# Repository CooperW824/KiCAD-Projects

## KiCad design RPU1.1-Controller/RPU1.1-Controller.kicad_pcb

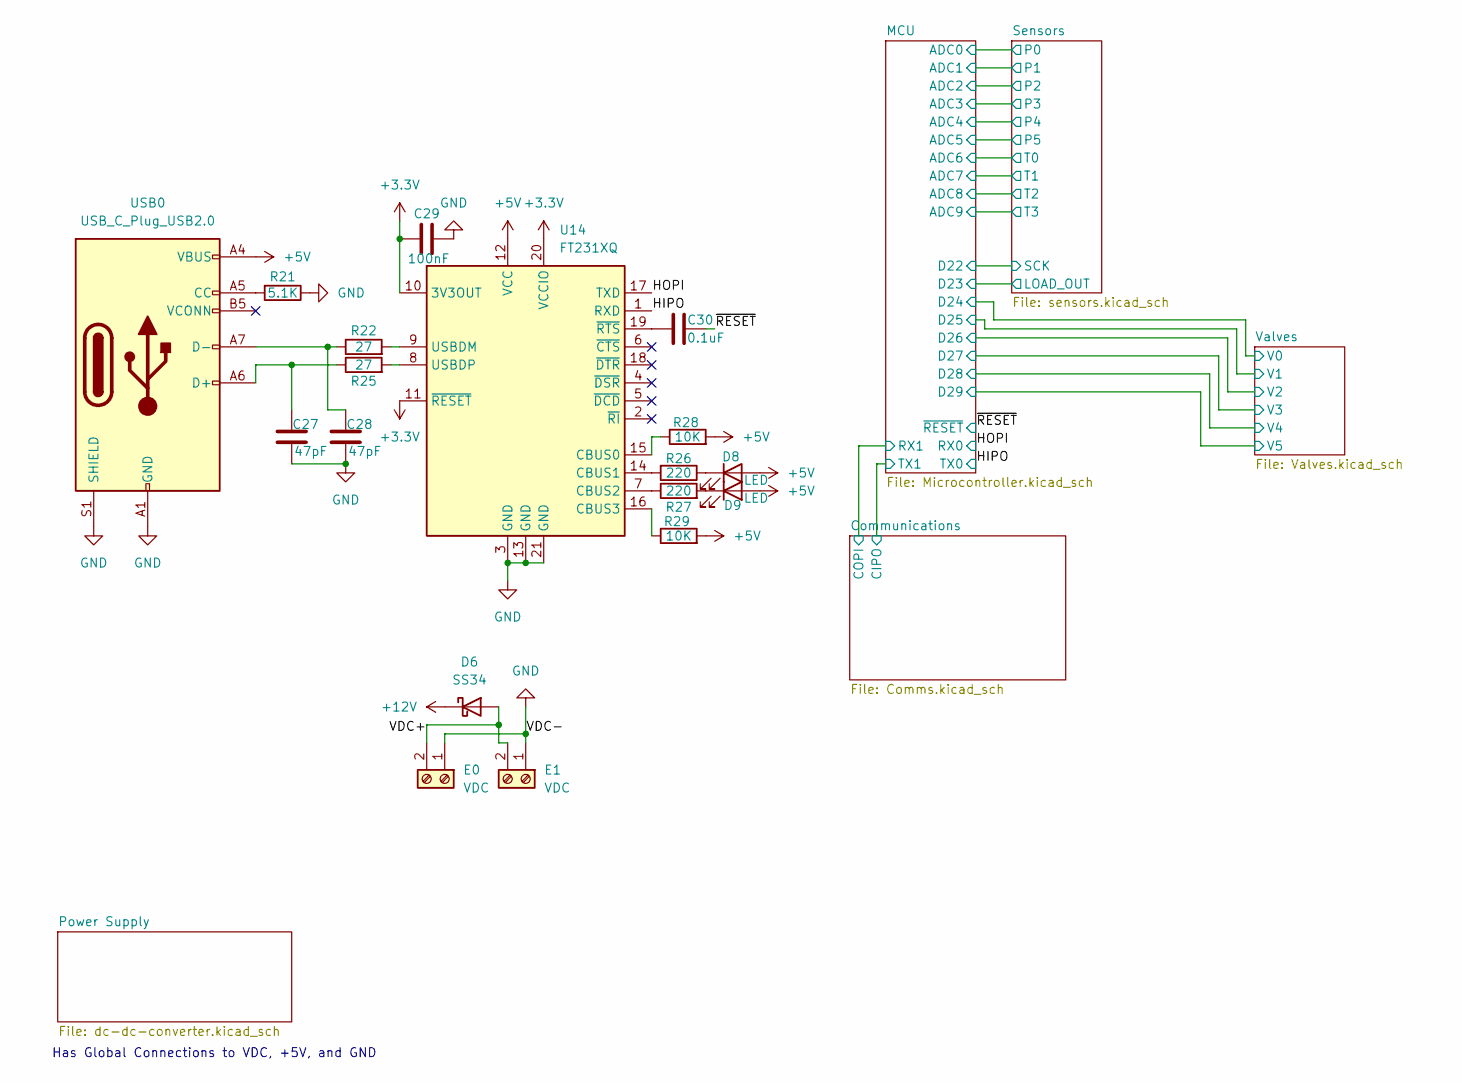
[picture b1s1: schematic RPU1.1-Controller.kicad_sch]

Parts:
C27, C28: 47pF; C_0603_1608Metric_Pad1.08x0.95mm_HandSolder
C29: 100nF; C_0603_1608Metric_Pad1.08x0.95mm_HandSolder
C30: 0.1uF; C_0603_1608Metric_Pad1.08x0.95mm_HandSolder
D6: SS34; D_SMA
D8, D9: LED; LED_0603_1608Metric
E0, E1: VDC; TerminalBlock_bornier-2_P5.08mm
R21: 5.1K; R_0603_1608Metric_Pad0.98x0.95mm_HandSolder
R22, R25: 27; R_0603_1608Metric_Pad0.98x0.95mm_HandSolder
R26, R27: 220; R_0603_1608Metric_Pad0.98x0.95mm_HandSolder
R28, R29: 10K; R_0603_1608Metric_Pad0.98x0.95mm_HandSolder
U14: FT231XQ; QFN-20-1EP_4x4mm_P0.5mm_EP2.5x2.5mm
USB0: USB_C_Plug_USB2.0; USB_C_Receptacle_Amphenol_12401610E4-2A

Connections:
+3.3V: C29.1, U14.10 (3V3OUT), U14.11 (~RESET), U14.20 (VCCIO)
+5V: D8.2 (A), D9.2 (A), R28.2, R29.2, U14.12 (VCC), USB0.A4 (VBUS), USB0.A9 (VBUS), USB0.B4 (VBUS), USB0.B9 (VBUS); also elsewhere on the board
+12V: D6.1 (K); also elsewhere on the board
/HIPO: U14.1 (RXD); also elsewhere on the board
/HOPI: U14.17 (TXD); also elsewhere on the board
/VDC+: D6.2 (A), E0.2, E1.2
/~RESET: C30.2; also elsewhere on the board
GND: C27.2, C28.2, C29.2, E0.1, E1.1, R21.1, U14.3 (GND), U14.13 (GND), U14.21 (GND), USB0.A1 (GND), USB0.A12 (GND), USB0.B1 (GND), USB0.B12 (GND), USB0.S1 (SHIELD); also elsewhere on the board
unnamed: D8.1 (K), R26.1
unnamed: D9.1 (K), R27.2
unnamed: R28.1, U14.15 (CBUS0)
unnamed: R26.2, U14.14 (CBUS1)
unnamed: R27.1, U14.7 (CBUS2)
unnamed: R29.1, U14.16 (CBUS3)
unnamed: R22.2, U14.9 (USBDM)
unnamed: R25.2, U14.8 (USBDP)
unnamed: C30.1, U14.19 (~RTS)
unnamed: R21.2, USB0.A5 (CC)
unnamed: C27.1, R25.1, USB0.A6 (D+)
unnamed: C28.1, R22.1, USB0.A7 (D-)

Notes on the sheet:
Has Global Connections to VDC, +5V, and GND

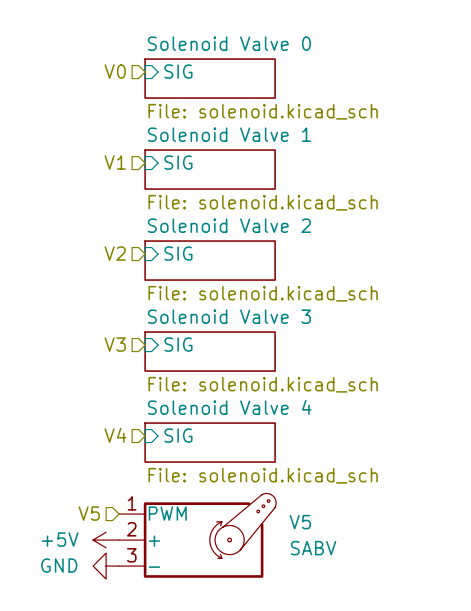
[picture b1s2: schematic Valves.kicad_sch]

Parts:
V5: SABV; TerminalBlock_bornier-3_P5.08mm

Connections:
+5V: V5.2 (+); also elsewhere on the board
/MCU/D29: V5.1 (PWM); also elsewhere on the board
GND: V5.3 (-); also elsewhere on the board

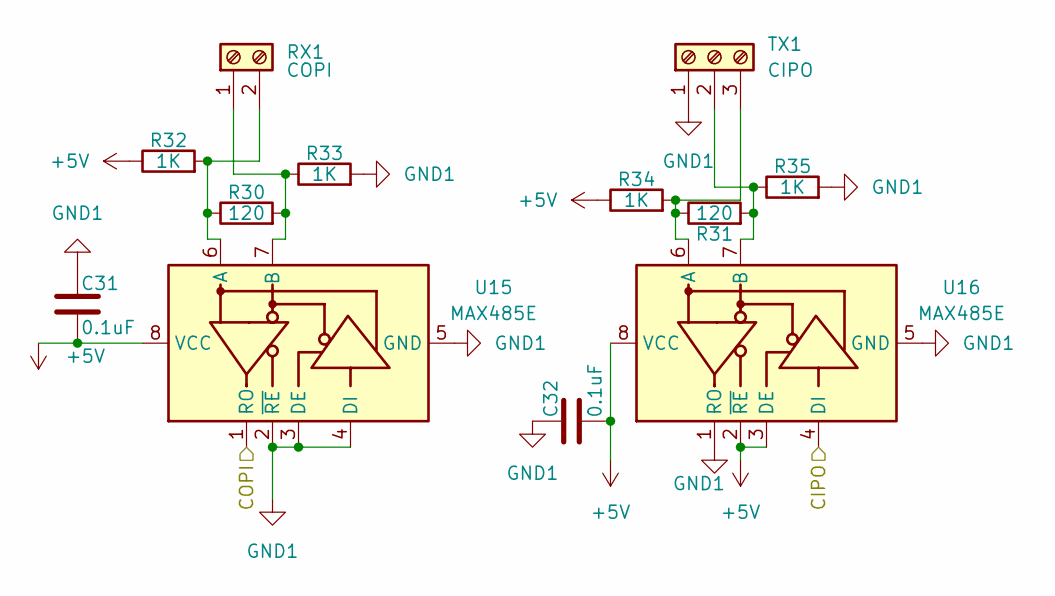
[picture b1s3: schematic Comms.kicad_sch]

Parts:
C31, C32: 0.1uF; C_0603_1608Metric_Pad1.08x0.95mm_HandSolder
R30, R31: 120; R_0603_1608Metric_Pad0.98x0.95mm_HandSolder
R32, R33, R34, R35: 1K; R_0603_1608Metric_Pad0.98x0.95mm_HandSolder
RX1: COPI; TerminalBlock_bornier-2_P5.08mm
TX1: CIPO; TerminalBlock_bornier-3_P5.08mm
U15, U16: MAX485E; SOIC-8_3.9x4.9mm_P1.27mm

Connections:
+5V: C31.2, C32.2, R32.1, R34.1, U15.8 (VCC), U16.2 (~RE), U16.3 (DE), U16.8 (VCC); also elsewhere on the board
/Communications/CIPO: U16.4 (DI); also elsewhere on the board
/Communications/COPI: U15.1 (RO); also elsewhere on the board
GND1: C31.1, C32.1, R33.2, R35.2, TX1.1, U15.2 (~RE), U15.3 (DE), U15.4 (DI), U15.5 (GND), U16.1 (RO), U16.5 (GND)
unnamed: R30.2, R33.1, RX1.1, U15.7 (B)
unnamed: R30.1, R32.2, RX1.2, U15.6 (A)
unnamed: R31.2, R35.1, TX1.2, U16.7 (B)
unnamed: R31.1, R34.2, TX1.3, U16.6 (A)

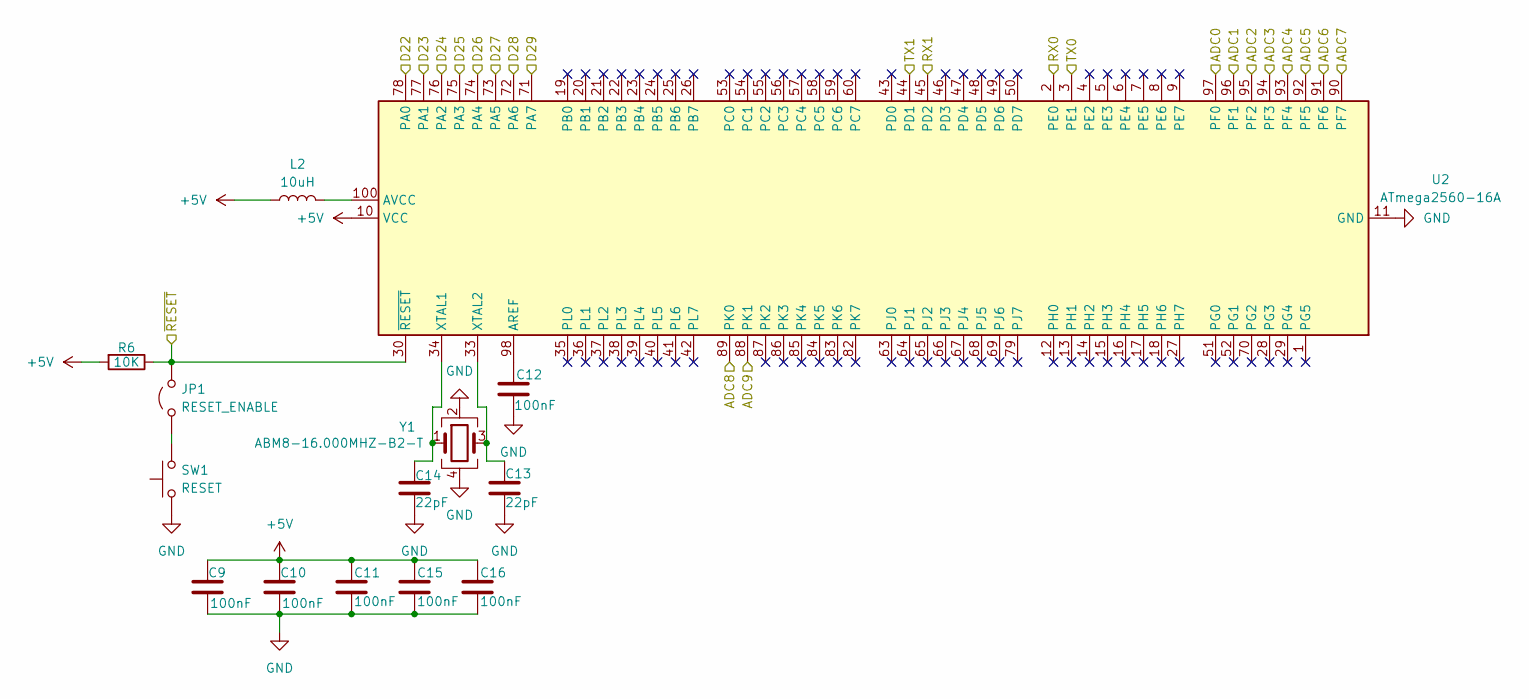
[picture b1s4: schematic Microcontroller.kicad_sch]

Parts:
C9, C10, C11, C12, C15, C16: 100nF; C_0603_1608Metric_Pad1.08x0.95mm_HandSolder
C13, C14: 22pF; C_0603_1608Metric_Pad1.08x0.95mm_HandSolder
JP1: RESET_ENABLE; PinHeader_1x02_P2.54mm_Vertical
L2: 10uH; L_0805_2012Metric_Pad1.15x1.40mm_HandSolder
R6: 10K; R_0603_1608Metric_Pad0.98x0.95mm_HandSolder
SW1: RESET; SW_PUSH_6mm
U2: ATmega2560-16A; TQFP-100_14x14mm_P0.5mm
Y1: ABM8-16.000MHZ-B2-T; Oscillator_SMD_Abracon_ASE-4Pin_3.2x2.5mm

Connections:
+5V: C9.1, C10.1, C11.1, C15.1, C16.1, L2.1, R6.2, U2.10 (VCC), U2.31 (VCC), U2.61 (VCC), U2.80 (VCC); also elsewhere on the board
/Communications/CIPO: U2.44 (PD1); also elsewhere on the board
/Communications/COPI: U2.45 (PD2); also elsewhere on the board
/HIPO: U2.3 (PE1); also elsewhere on the board
/HOPI: U2.2 (PE0); also elsewhere on the board
/MCU/ADC0: U2.97 (PF0); also elsewhere on the board
/MCU/ADC1: U2.96 (PF1); also elsewhere on the board
/MCU/ADC2: U2.95 (PF2); also elsewhere on the board
/MCU/ADC3: U2.94 (PF3); also elsewhere on the board
/MCU/ADC4: U2.93 (PF4); also elsewhere on the board
/MCU/ADC5: U2.92 (PF5); also elsewhere on the board
/MCU/ADC6: U2.91 (PF6); also elsewhere on the board
/MCU/ADC7: U2.90 (PF7); also elsewhere on the board
/MCU/ADC8: U2.89 (PK0); also elsewhere on the board
/MCU/ADC9: U2.88 (PK1); also elsewhere on the board
/MCU/D22: U2.78 (PA0); also elsewhere on the board
/MCU/D23: U2.77 (PA1); also elsewhere on the board
/MCU/D24: U2.76 (PA2); also elsewhere on the board
/MCU/D25: U2.75 (PA3); also elsewhere on the board
/MCU/D26: U2.74 (PA4); also elsewhere on the board
/MCU/D27: U2.73 (PA5); also elsewhere on the board
/MCU/D28: U2.72 (PA6); also elsewhere on the board
/MCU/D29: U2.71 (PA7); also elsewhere on the board
/~RESET: JP1.2 (B), R6.1, U2.30 (~RESET); also elsewhere on the board
GND: C9.2, C10.2, C11.2, C12.2, C13.2, C14.2, C15.2, C16.2, SW1.1, U2.11 (GND), U2.32 (GND), U2.62 (GND), U2.81 (GND), U2.99 (GND), Y1.2, Y1.4; also elsewhere on the board
unnamed: JP1.1 (A), SW1.2
unnamed: C12.1, U2.98 (AREF)
unnamed: L2.2, U2.100 (AVCC)
unnamed: C14.1, U2.34 (XTAL1), Y1.1
unnamed: C13.1, U2.33 (XTAL2), Y1.3

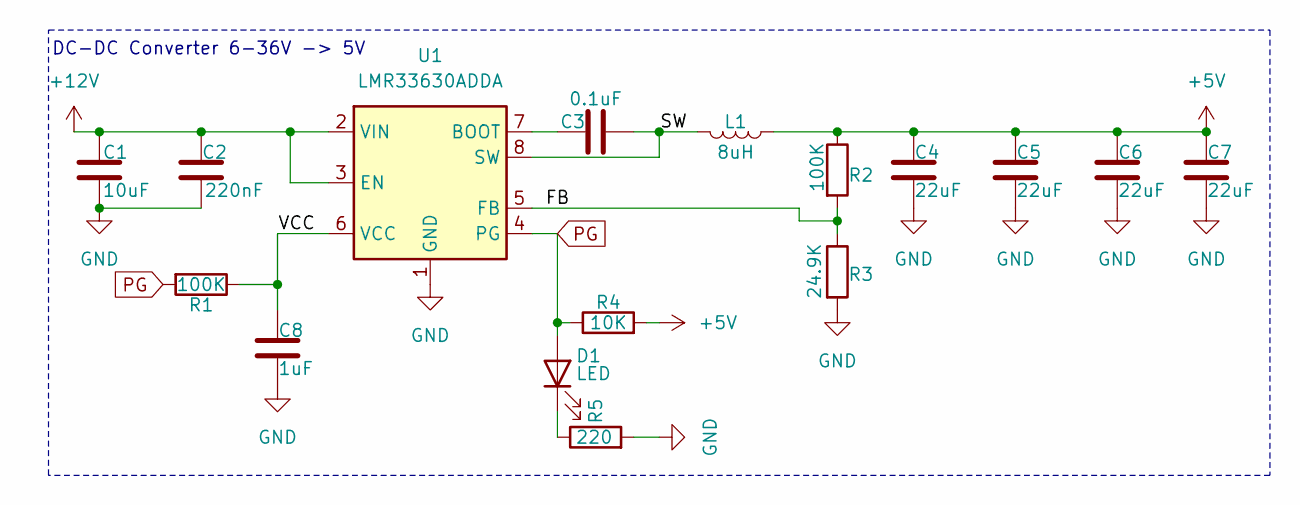
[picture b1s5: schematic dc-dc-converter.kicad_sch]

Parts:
C1: 10uF; C_0603_1608Metric
C2: 220nF; C_0402_1005Metric
C3: 0.1uF; C_0402_1005Metric
C4, C5, C6, C7: 22uF; C_0603_1608Metric
C8: 1uF; C_0402_1005Metric
D1: LED; LED_0603_1608Metric
L1: 8uH; L_0805_2012Metric
R1, R2: 100K; R_0603_1608Metric_Pad0.98x0.95mm_HandSolder
R3: 24.9K; R_0603_1608Metric_Pad0.98x0.95mm_HandSolder
R4: 10K; R_0603_1608Metric_Pad0.98x0.95mm_HandSolder
R5: 220; R_0603_1608Metric_Pad0.98x0.95mm_HandSolder
U1: LMR33630ADDA; Texas_HSOP-8-1EP_3.9x4.9mm_P1.27mm_ThermalVias

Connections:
+5V: C4.2, C5.2, C6.2, C7.2, L1.1, R2.1, R4.2; also elsewhere on the board
+12V: C1.1, C2.1, U1.2 (VIN), U1.3 (EN); also elsewhere on the board
/Power Supply/FB: R2.2, R3.1, U1.5 (FB)
/Power Supply/SW: C3.2, L1.2, U1.8 (SW)
/Power Supply/VCC: C8.2, R1.1, U1.6 (VCC)
GND: C1.2, C2.2, C4.1, C5.1, C6.1, C7.1, C8.1, R3.2, R5.2, U1.1 (GND), U1.9 (GND); also elsewhere on the board
unnamed: D1.1 (K), R5.1
unnamed: C3.1, U1.7 (BOOT)
PG: D1.2 (A), R1.2, R4.1, U1.4 (PG)

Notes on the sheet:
DC-DC Converter 6-36V -> 5V

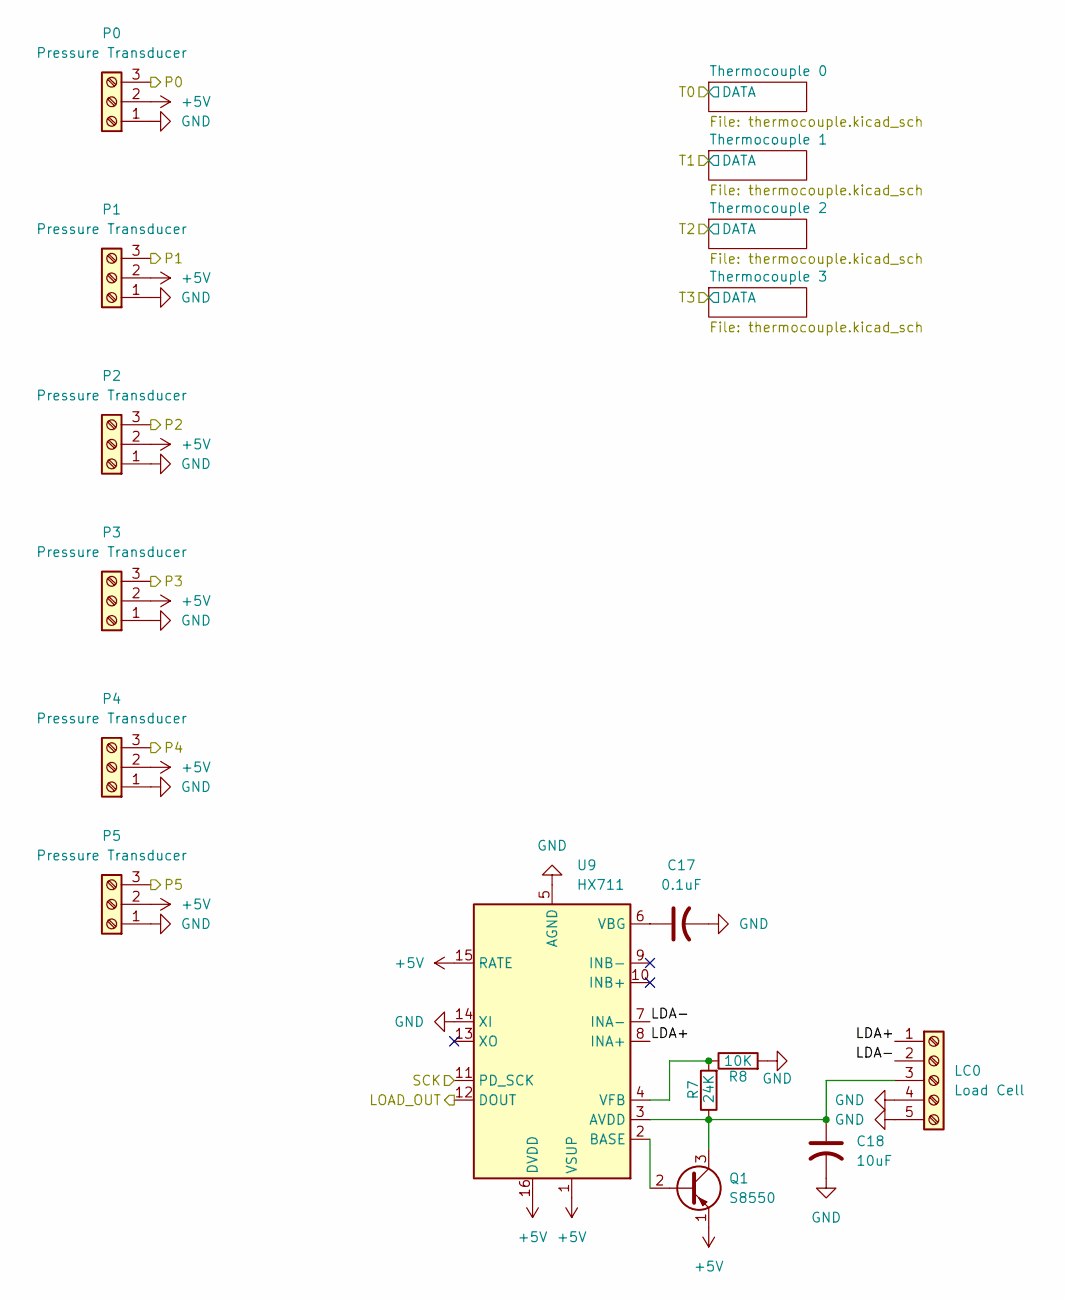
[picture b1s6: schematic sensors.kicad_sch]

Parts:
C17: 0.1uF; C_0603_1608Metric_Pad1.08x0.95mm_HandSolder
C18: 10uF; C_0603_1608Metric_Pad1.08x0.95mm_HandSolder
LC0: Load Cell; TerminalBlock_bornier-5_P5.08mm
P0, P1, P2, P3, P4, P5: Pressure Transducer; TerminalBlock_bornier-3_P5.08mm
Q1: S8550; SOT-23
R7: 24K; R_0603_1608Metric_Pad0.98x0.95mm_HandSolder
R8: 10K; R_0603_1608Metric_Pad0.98x0.95mm_HandSolder
U9: HX711; SOP-16_3.9x9.9mm_P1.27mm

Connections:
+5V: P0.2, P1.2, P2.2, P3.2, P4.2, P5.2, Q1.1 (E), U9.1 (VSUP), U9.15 (RATE), U9.16 (DVDD); also elsewhere on the board
/MCU/ADC0: P0.3; also elsewhere on the board
/MCU/ADC1: P1.3; also elsewhere on the board
/MCU/ADC2: P2.3; also elsewhere on the board
/MCU/ADC3: P3.3; also elsewhere on the board
/MCU/ADC4: P4.3; also elsewhere on the board
/MCU/ADC5: P5.3; also elsewhere on the board
/MCU/D22: U9.11 (PD_SCK); also elsewhere on the board
/MCU/D23: U9.12 (DOUT); also elsewhere on the board
/Sensors/LDA+: LC0.1, U9.8 (INA+)
/Sensors/LDA-: LC0.2, U9.7 (INA-)
GND: C17.2, C18.2, LC0.4, LC0.5, P0.1, P1.1, P2.1, P3.1, P4.1, P5.1, R8.2, U9.5 (AGND), U9.14 (XI); also elsewhere on the board
unnamed: C18.1, LC0.3, Q1.3 (C), R7.1, U9.3 (AVDD)
unnamed: Q1.2 (B), U9.2 (BASE)
unnamed: C17.1, U9.6 (VBG)
unnamed: R7.2, R8.1, U9.4 (VFB)

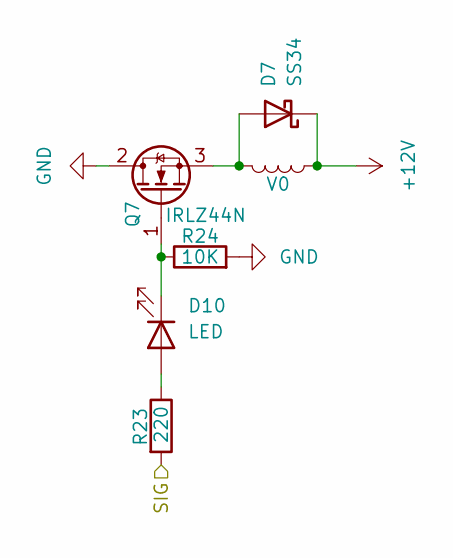
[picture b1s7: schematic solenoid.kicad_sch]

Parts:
D7: SS34; D_SMA
D10: LED; LED_D5.0mm
Q7: IRLZ44N; TO-220-3_Vertical
R23: 220; R_0603_1608Metric_Pad0.98x0.95mm_HandSolder
R24: 10K; R_0603_1608Metric_Pad0.98x0.95mm_HandSolder
V0: L; TerminalBlock_bornier-2_P5.08mm

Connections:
+12V: D7.1 (K), V0.1; also elsewhere on the board
/MCU/D24: R23.2; also elsewhere on the board
GND: Q7.2 (D), R24.2; also elsewhere on the board
unnamed: D7.2 (A), Q7.3 (S), V0.2
unnamed: D10.2 (A), R23.1
unnamed: D10.1 (K), Q7.1 (G), R24.1

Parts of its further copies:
D2, D3, D4, D5: SS34; D_SMA
D11, D12, D13, D14: LED; LED_D5.0mm
Q2, Q3, Q4, Q5: IRLZ44N; TO-220-3_Vertical
R13, R15, R17, R19: 220; R_0603_1608Metric_Pad0.98x0.95mm_HandSolder
R14, R16, R18, R20: 10K; R_0603_1608Metric_Pad0.98x0.95mm_HandSolder
V1, V2, V3, V4: L; TerminalBlock_bornier-2_P5.08mm

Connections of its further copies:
+12V: D2.1 (K), D3.1 (K), D4.1 (K), D5.1 (K), V1.1, V2.1, V3.1, V4.1; also elsewhere on the board
/MCU/D25: R13.2; also elsewhere on the board
/MCU/D26: R15.2; also elsewhere on the board
/MCU/D27: R17.2; also elsewhere on the board
/MCU/D28: R19.2; also elsewhere on the board
GND: Q2.2 (D), Q3.2 (D), Q4.2 (D), Q5.2 (D), R14.2, R16.2, R18.2, R20.2; also elsewhere on the board
unnamed: D2.2 (A), Q2.3 (S), V1.2
unnamed: D3.2 (A), Q3.3 (S), V2.2
unnamed: D4.2 (A), Q4.3 (S), V3.2
unnamed: D5.2 (A), Q5.3 (S), V4.2
unnamed: D11.2 (A), R15.1
unnamed: D11.1 (K), Q3.1 (G), R16.1
unnamed: D12.2 (A), R13.1
unnamed: D12.1 (K), Q2.1 (G), R14.1
unnamed: D13.2 (A), R17.1
unnamed: D13.1 (K), Q4.1 (G), R18.1
unnamed: D14.2 (A), R19.1
unnamed: D14.1 (K), Q5.1 (G), R20.1

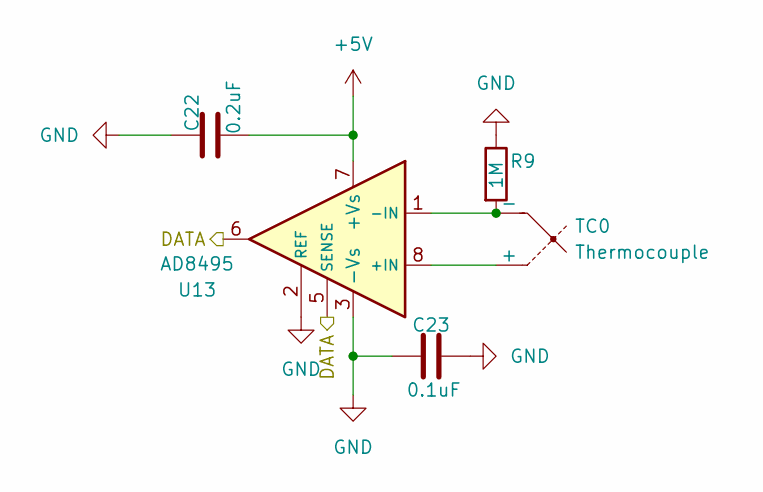
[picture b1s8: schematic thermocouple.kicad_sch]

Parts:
C22: 0.2uF; C_0603_1608Metric_Pad1.08x0.95mm_HandSolder
C23: 0.1uF; C_0603_1608Metric_Pad1.08x0.95mm_HandSolder
R9: 1M; R_0603_1608Metric_Pad0.98x0.95mm_HandSolder
TC0: Thermocouple; TerminalBlock_bornier-2_P5.08mm
U13: AD8495; MSOP-8_3x3mm_P0.65mm

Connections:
+5V: C22.2, U13.7 (+Vs); also elsewhere on the board
/MCU/ADC6: U13.5 (SENSE), U13.6; also elsewhere on the board
GND: C22.1, C23.1, C23.2, R9.1, U13.2 (REF), U13.3 (-Vs); also elsewhere on the board
unnamed: TC0.2 (+), U13.8 (+IN)
unnamed: R9.2, TC0.1 (-), U13.1 (-IN)

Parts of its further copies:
C20, C24, C26: 0.1uF; C_0603_1608Metric_Pad1.08x0.95mm_HandSolder
R10, R11, R12: 1M; R_0603_1608Metric_Pad0.98x0.95mm_HandSolder
TC1, TC2, TC3: Thermocouple; TerminalBlock_bornier-2_P5.08mm
U10, U11, U12: AD8495; MSOP-8_3x3mm_P0.65mm

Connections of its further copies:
+5V: U10.7 (+Vs), U11.7 (+Vs), U12.7 (+Vs); also elsewhere on the board
/MCU/ADC7: U10.5 (SENSE), U10.6; also elsewhere on the board
/MCU/ADC8: U11.5 (SENSE), U11.6; also elsewhere on the board
/MCU/ADC9: U12.5 (SENSE), U12.6; also elsewhere on the board
GND: C20.1, C20.2, C24.1, C24.2, C26.1, C26.2, R10.1, R11.1, R12.1, U10.2 (REF), U10.3 (-Vs), U11.2 (REF), U11.3 (-Vs), U12.2 (REF), U12.3 (-Vs); also elsewhere on the board
unnamed: TC1.2 (+), U10.8 (+IN)
unnamed: R10.2, TC1.1 (-), U10.1 (-IN)
unnamed: TC2.2 (+), U11.8 (+IN)
unnamed: R11.2, TC2.1 (-), U11.1 (-IN)
unnamed: TC3.2 (+), U12.8 (+IN)
unnamed: R12.2, TC3.1 (-), U12.1 (-IN)

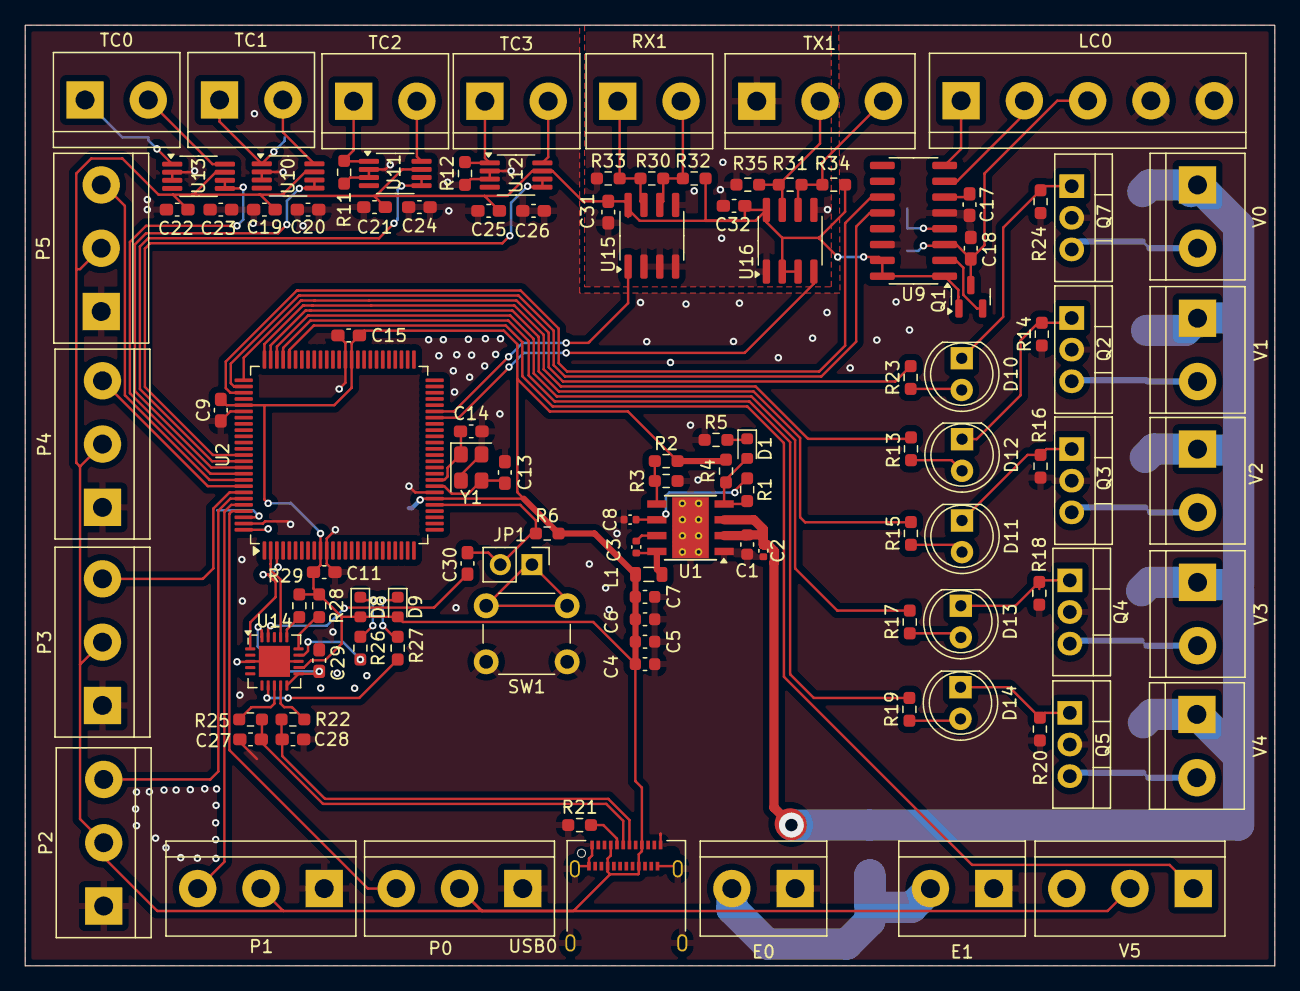
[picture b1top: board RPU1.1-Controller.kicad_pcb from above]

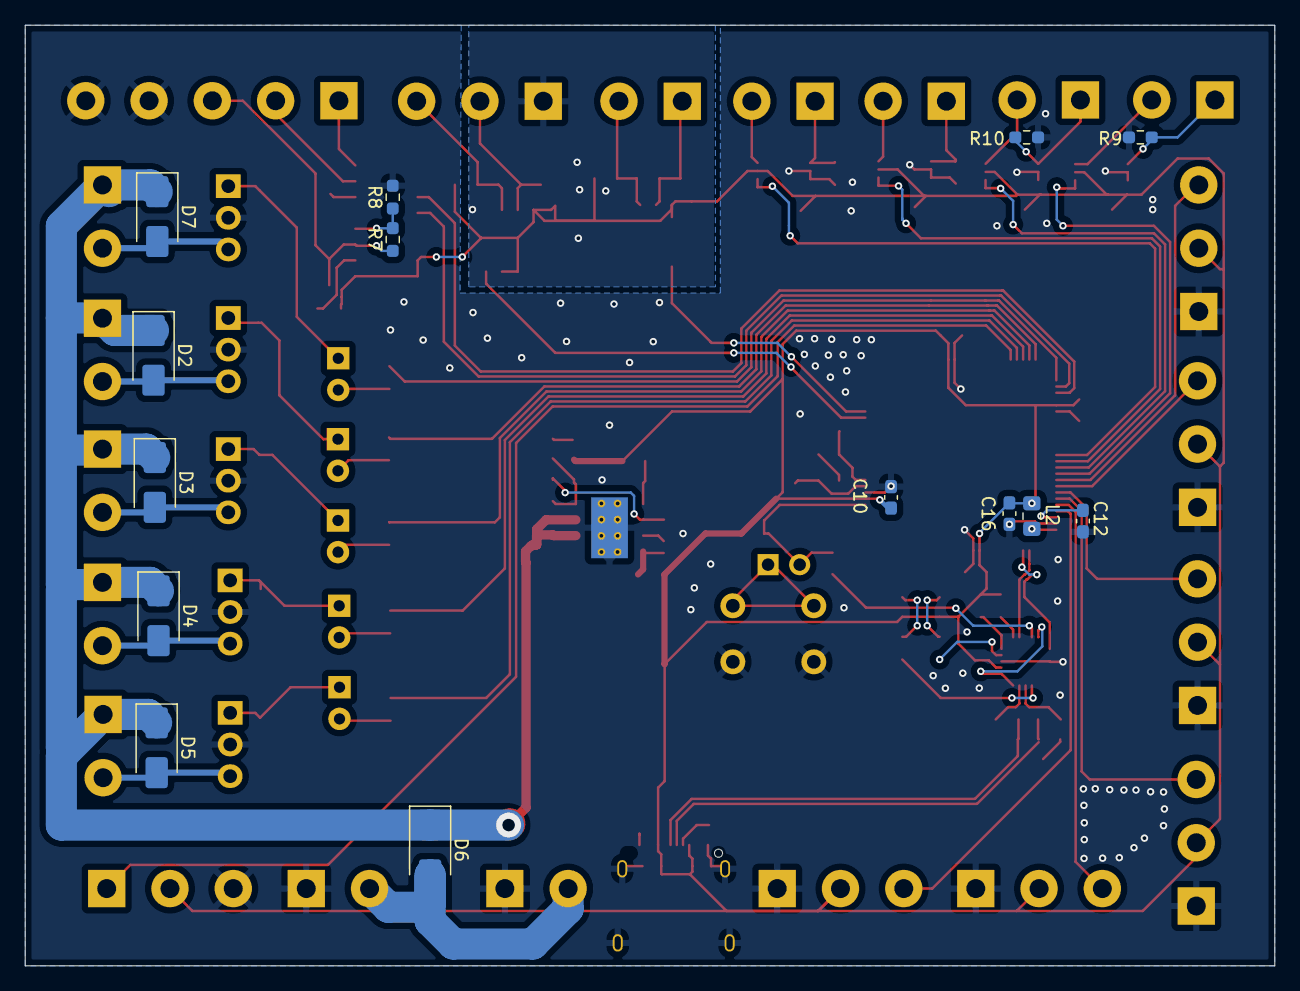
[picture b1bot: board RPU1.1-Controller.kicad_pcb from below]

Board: 2 copper layers, 100.3 x 75.5 mm, 124 parts (14 on the bottom side), 85 nets.

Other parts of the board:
C19, C21, C25: 0.1uF; C_0603_1608Metric_Pad1.08x0.95mm_HandSolder

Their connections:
+5V: C19.2, C21.2, C25.2; also elsewhere on the board
GND: C19.1, C21.1, C25.1; also elsewhere on the board

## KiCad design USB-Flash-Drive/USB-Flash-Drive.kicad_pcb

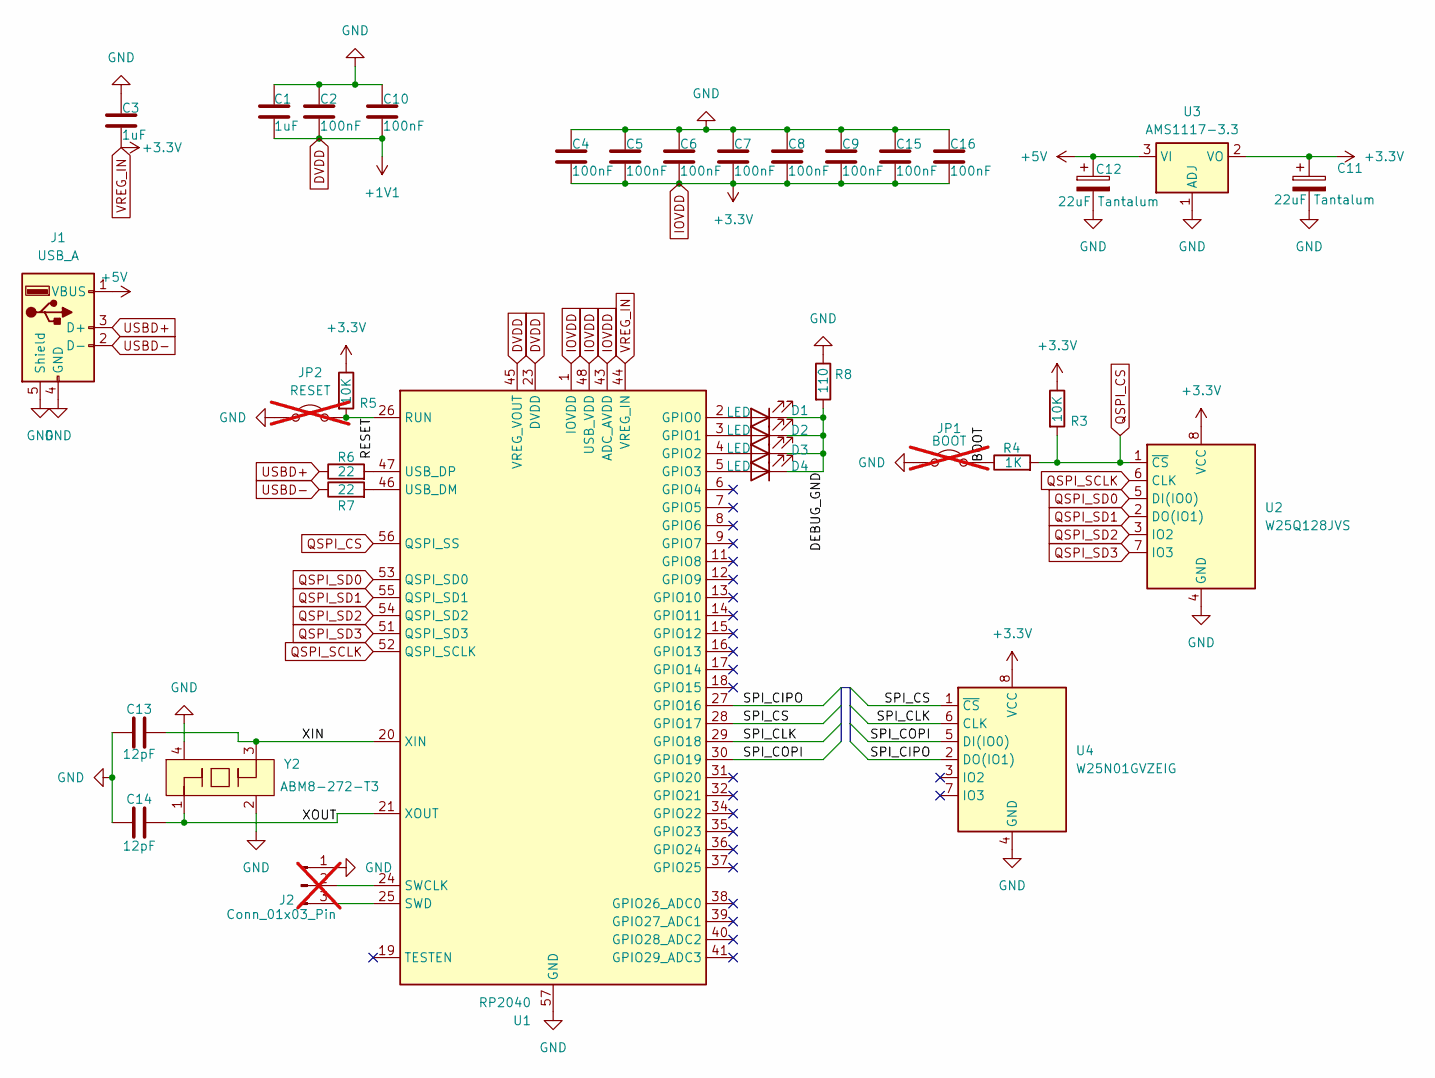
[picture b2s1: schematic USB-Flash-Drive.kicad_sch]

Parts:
C1, C3: 1uF; C_0402_1005Metric
C2, C4, C5, C6, C7, C8, C9, C10, C15, C16: 100nF; C_0402_1005Metric
C11, C12: 22uF Tantalum; C_1206_3216Metric
C13, C14: 12pF; C_0402_1005Metric
D1, D2, D3, D4: LED; LED_0402_1005Metric
J1: USB_A; USB_A_Molex_48037-2200_Horizontal
J2: Conn_01x03_Pin; PinHeader_1x03_P2.54mm_Vertical; not fitted
JP1: BOOT; PinHeader_1x02_P2.54mm_Vertical; not fitted
JP2: RESET; PinHeader_1x02_P2.54mm_Vertical; not fitted
R3, R5: 10K; R_0402_1005Metric
R4: 1K; R_0402_1005Metric
R6, R7: 22; R_0402_1005Metric
R8: 110; R_0402_1005Metric
U1: RP2040; QFN-56-1EP_7x7mm_P0.4mm_EP3.2x3.2mm
U2: W25Q128JVS; SOIC-8_5.3x5.3mm_P1.27mm
U3: AMS1117-3.3; SOT-223-3_TabPin2
U4: W25N01GVZEIG; WSON-8-1EP_8x6mm_P1.27mm_EP3.4x4.3mm
Y2: ABM8-272-T3; Oscillator_SMD_EuroQuartz_XO32-4Pin_3.2x2.5mm

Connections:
+5V: C12.1, J1.1 (VBUS), U3.3 (VI)
/BOOT: JP1.2 (B), R4.1
/DEBUG_GND: D1.1 (K), D2.1 (K), D3.1 (K), D4.1 (K), R8.2
/RESET: JP2.2 (B), R5.2, U1.26 (RUN)
/SPI_CIPO: U1.27 (GPIO16), U4.2 (DO(IO1))
/SPI_CLK: U1.29 (GPIO18), U4.6 (CLK)
/SPI_COPI: U1.30 (GPIO19), U4.5 (DI(IO0))
/SPI_CS: U1.28 (GPIO17), U4.1 (~CS)
/XIN: C13.1, U1.20 (XIN), Y2.3
/XOUT: C14.1, U1.21 (XOUT), Y2.1
DVDD: C1.1, C2.2, C10.2, U1.23 (DVDD), U1.45 (VREG_VOUT), U1.50 (DVDD)
GND: C1.2, C2.1, C3.1, C4.1, C5.1, C6.1, C7.1, C8.1, C9.1, C10.1, C11.2, C12.2, C13.2, C14.2, C15.1, C16.1, J1.4 (GND), J1.5 (Shield), J2.1, JP1.1 (A), JP2.1 (A), R8.1, U1.57 (GND), U2.4 (GND), U3.1 (ADJ), U4.4 (GND), Y2.2, Y2.4
IOVDD: C3.2, C4.2, C5.2, C6.2, C7.2, C8.2, C9.2, C11.1, C15.2, C16.2, R3.1, R5.1, U1.1 (IOVDD), U1.10 (IOVDD), U1.22 (IOVDD), U1.33 (IOVDD), U1.42 (IOVDD), U1.43 (ADC_AVDD), U1.44 (VREG_IN), U1.48 (USB_VDD), U1.49 (IOVDD), U2.8 (VCC), U3.2 (VO), U4.8 (VCC)
unnamed: D1.2 (A), U1.2 (GPIO0)
unnamed: D2.2 (A), U1.3 (GPIO1)
unnamed: D3.2 (A), U1.4 (GPIO2)
unnamed: D4.2 (A), U1.5 (GPIO3)
unnamed: J2.2, U1.24 (SWCLK)
unnamed: J2.3, U1.25 (SWD)
unnamed: R7.2, U1.46 (USB_DM)
unnamed: R6.2, U1.47 (USB_DP)
QSPI_CS: R3.2, R4.2, U1.56 (QSPI_SS), U2.1 (~CS)
QSPI_SCLK: U1.52 (QSPI_SCLK), U2.6 (CLK)
QSPI_SD0: U1.53 (QSPI_SD0), U2.5 (DI(IO0))
QSPI_SD1: U1.55 (QSPI_SD1), U2.2 (DO(IO1))
QSPI_SD2: U1.54 (QSPI_SD2), U2.3 (IO2)
QSPI_SD3: U1.51 (QSPI_SD3), U2.7 (IO3)
USBD+: J1.3 (D+), R6.1
USBD-: J1.2 (D-), R7.1

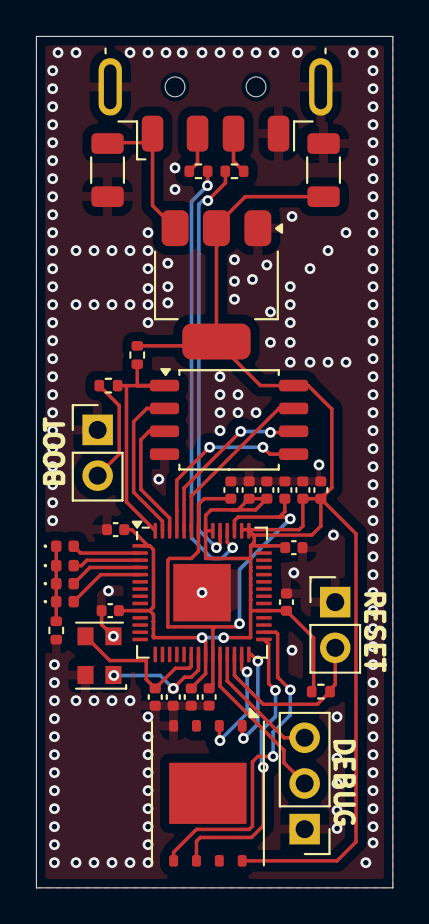
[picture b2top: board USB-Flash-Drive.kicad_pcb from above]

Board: 2 copper layers, 19.8 x 47.3 mm, 35 parts (0 on the bottom side), 29 nets.

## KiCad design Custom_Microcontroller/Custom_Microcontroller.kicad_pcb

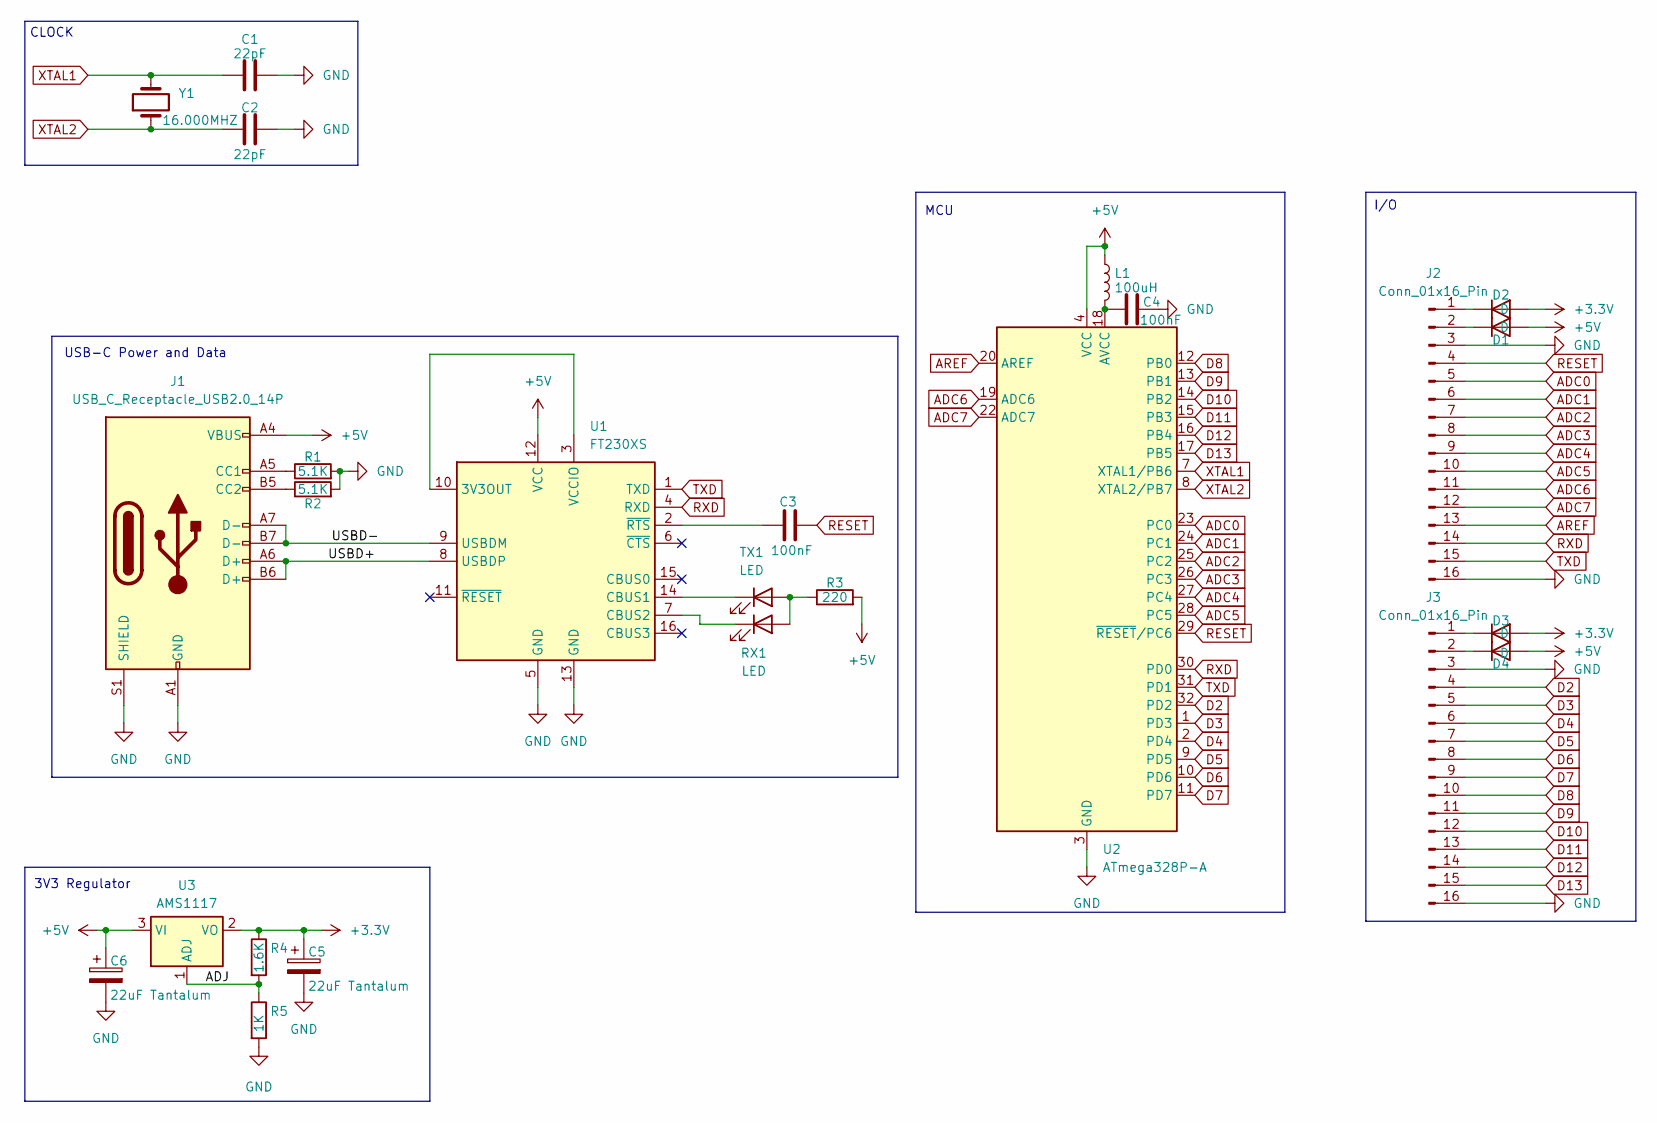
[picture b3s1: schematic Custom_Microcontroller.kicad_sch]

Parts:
C1, C2: 22pF; C_0603_1608Metric_Pad1.08x0.95mm_HandSolder
C3, C4: 100nF; C_0402_1005Metric_Pad0.74x0.62mm_HandSolder
C5, C6: 22uF Tantalum; CP_EIA-3216-10_Kemet-I_HandSolder
D1, D2, D3, D4: D; D_SMA
J1: USB_C_Receptacle_USB2.0_14P; USB_C_Receptacle_HRO_TYPE-C-31-M-12
J2, J3: Conn_01x16_Pin; PinHeader_1x16_P2.54mm_Vertical
L1: 100uH; L_1210_3225Metric_Pad1.42x2.65mm_HandSolder
R1, R2: 5.1K; R_0603_1608Metric_Pad0.98x0.95mm_HandSolder
R3: 220; R_0603_1608Metric_Pad0.98x0.95mm_HandSolder
R4: 1.6K; R_0603_1608Metric_Pad0.98x0.95mm_HandSolder
R5: 1K; R_0603_1608Metric_Pad0.98x0.95mm_HandSolder
RX1: LED; LED_0201_0603Metric_Pad0.64x0.40mm_HandSolder
TX1: LED; LED_0201_0603Metric_Pad0.64x0.40mm_HandSolder
U1: FT230XS; SSOP-16_3.9x4.9mm_P0.635mm
U2: ATmega328P-A; TQFP-32_7x7mm_P0.8mm
U3: AMS1117; SOT-223-3_TabPin2
Y1: 16.000MHZ; 28AX

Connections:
+3.3V: C5.1, D2.2 (A), D3.2 (A), R4.1, U3.2 (VO)
+5V: C6.1, D1.2 (A), D4.2 (A), J1.A4 (VBUS), J1.A9 (VBUS), J1.B4 (VBUS), J1.B9 (VBUS), L1.1, R3.2, U1.12 (VCC), U2.4 (VCC), U2.6 (VCC), U3.3 (VI)
/ADJ: R4.2, R5.1, U3.1 (ADJ)
/USBD+: J1.A6 (D+), J1.B6 (D+), U1.8 (USBDP)
/USBD-: J1.A7 (D-), J1.B7 (D-), U1.9 (USBDM)
ADC0: J2.5, U2.23 (PC0)
ADC1: J2.6, U2.24 (PC1)
ADC2: J2.7, U2.25 (PC2)
ADC3: J2.8, U2.26 (PC3)
ADC4: J2.9, U2.27 (PC4)
ADC5: J2.10, U2.28 (PC5)
ADC6: J2.11, U2.19 (ADC6)
ADC7: J2.12, U2.22 (ADC7)
AREF: J2.13, U2.20 (AREF)
D2: J3.4, U2.32 (PD2)
D3: J3.5, U2.1 (PD3)
D4: J3.6, U2.2 (PD4)
D5: J3.7, U2.9 (PD5)
D6: J3.8, U2.10 (PD6)
D7: J3.9, U2.11 (PD7)
D8: J3.10, U2.12 (PB0)
D9: J3.11, U2.13 (PB1)
D10: J3.12, U2.14 (PB2)
D11: J3.13, U2.15 (PB3)
D12: J3.14, U2.16 (PB4)
D13: J3.15, U2.17 (PB5)
GND: C1.2, C2.2, C4.2, C5.2, C6.2, J1.A1 (GND), J1.A12 (GND), J1.B1 (GND), J1.B12 (GND), J1.S1 (SHIELD), J2.3, J2.16, J3.3, J3.16, R1.2, R2.2, R5.2, U1.5 (GND), U1.13 (GND), U2.3 (GND), U2.5 (GND), U2.21 (GND)
unnamed: D1.1 (K), J2.2
unnamed: D2.1 (K), J2.1
unnamed: D3.1 (K), J3.1
unnamed: D4.1 (K), J3.2
unnamed: J1.A5 (CC1), R1.1
unnamed: J1.B5 (CC2), R2.1
unnamed: R3.1, RX1.2 (A), TX1.2 (A)
unnamed: RX1.1 (K), U1.7 (CBUS2)
unnamed: TX1.1 (K), U1.14 (CBUS1)
unnamed: U1.3 (VCCIO), U1.10 (3V3OUT)
unnamed: C3.1, U1.2 (~RTS)
unnamed: C4.1, L1.2, U2.18 (AVCC)
RESET: C3.2, J2.4, U2.29 (~RESET/PC6)
RXD: J2.14, U1.4 (RXD), U2.30 (PD0)
TXD: J2.15, U1.1 (TXD), U2.31 (PD1)
XTAL1: C1.1, U2.7 (XTAL1/PB6), Y1.4
XTAL2: C2.1, U2.8 (XTAL2/PB7), Y1.1

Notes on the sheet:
MCU
3V3 Regulator
USB-C Power and Data
CLOCK
I/O

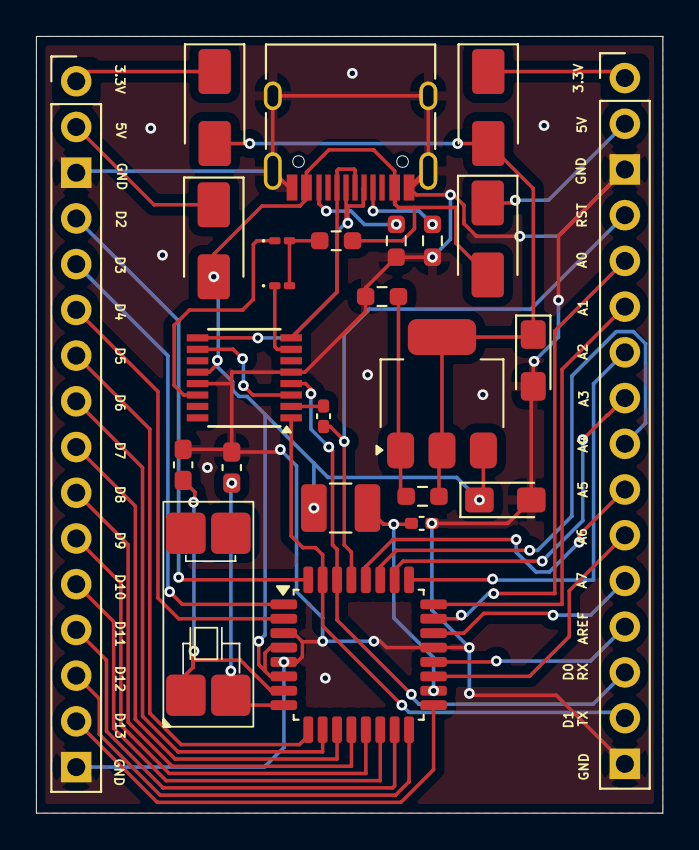
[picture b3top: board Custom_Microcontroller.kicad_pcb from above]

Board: 2 copper layers, 34.8 x 43.1 mm, 25 parts (0 on the bottom side), 44 nets.
